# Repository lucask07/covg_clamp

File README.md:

# COVG Clamp Board 

Schematic and layout for the COVG bath and guard clamps. This board sits near electrodes and includes a force output and a high-impedance feedback input to create a closed-loop clamp. Intention is to use the same design for the bath and guard clamps of a COVG amplifiers. The board supports digital programming of the current measurement gain and the feedback loop stability. Switching on the board allows for connect and disconnect of electrodes and injection (or measurements) of calibration signals onto an electrode.

### The PDF plot of the board schematic is [here](docs/bath_clamp.pdf) 
- 2D capture of the 3D model of the clamp board layout: 
<p align="center">

## Acknowledgements 

If this work contributes to your research please cite:

I. Delgadillo Bonequi, A. Stroschein, and L. J. Koerner, “A field-programmable gate array (FPGA)-based data acquisition system for closed-loop experiments,” Review of Scientific Instruments, vol. 93, no. 11, p. 114712, Nov. 2022, [doi: 10.1063/5.0121898](http://doi.org/10.1063/5.0121898).

## HDMI: connection from DAQ to daughtercard 

The digital COVG project uses the concept of one main data acquition board connected to an FPGA. The main data acquisition board has multiple channels that extend to daughtercards. The connection to each daughtercard allows for low-latency control by connections to high-speed ADCs and DACs on the daq board. For COVG the daughtercards are the bath clamp; the guard clamp; the voltage clamp and I force; and the V1/V2. The connectivity to the daughtercard is generalized and will be the same for each. 

An HDMI-A cable is used for input and output signals that connects the bath clamp daughtercard to the DAQ board. The HDMI cable carries:

- **power**: +5V, +15V, -15V
- **GND** 
- **Analog outputs** (to ADCs): 
	- OUT\_P, OUT\_N differential pair (x1) to 5 MSPS ADC 
	- single-ended out AMP\_OUT, CAL\_ADC both to individual channel of 1 MSPS ADC (ADS8686) 
- **Analog reference**: VCM: buffered ADC common-mode voltage (nominal 2.5 V)
- **Digital inputs** (from DACs): 
	- CMD: (command signal) from 1 us settling time DAC (attenuated by x10 at board)
	- CC: (capacitive compensation) from 1 us settling time DAC. AC coupled. 
	- CAL_DAC: from 5 us settling time DAC (DAC8050). Either voltage source or current source (Howland current pump), programmable on DAQ board
- **Digital control** (I2C): SDA, SCL (@ 3.3 V levels). Pull-ups are on DAQ board not on the daughtercards! The daughtercards use a TCA9555 I/O expander to generate many control signals from the I2C interface. 
- **Utiility** grab-bag connected to test-point. Jumper on DAQ board to set to analog in, analog out or digital I/O.

| Pin | HDMI name    | Generic Daughtercard     | Bath clamp | Notes  |
|-----|--------------|--------------|------------|---------------------------------------------------------------------------|
| 1   | Data2+       | fastDAC1     | CMD        | ~1 us settling time                      |
| 2   | Data2 shield | Gnd          | Gnd        |                                                                           |
| 3   | Data2-       | Analog/GPIO1 | CAL_DAC    | Analog input signal from DAC8050, 16 bit, 5us settle, 5 V supply                                                                         |
| 4   | Data1+       | fastADC+     | IM_P       | to AD7960/AD7961. Differential low-pass filter on DAQ board                                                                          |
| 5   | Data1 shield | Gnd          | Gnd        |                                                                           |
| 6   | Data1-       | fastADC-     | IM_N       | to AD7960/AD7961. Differential low-pass filter on DAQ board                                                                          |
| 7   | Data0+       | fastDAC2     | CC         | ~1 us settling time                                                                          |
| 8   | Data0 shield | Gnd          | Gnd        |                                                                           |
| 9   | Data0-       | Analog/GPIO2 | CAL_ADC    | to ADS8686 1 MSPS, programmable PGA for range up to +/-10V                                                           |
| 10  | Clock+       | 15V          | 15V        | From a linear regulator on the DAQ board, 75 mA max per channel                                                                         |
| 11  | Clock shield | Gnd          | Gnd        |                                                                           |
| 12  | Clock-       | VCM          | VCM        | buffered on DAQ board, nominal 2.5 V                                                                          |
| 13  | CEC          | -15V         | -15V       | From a linear regulator on the DAQ board, 75 mA max per channel                             |
| 14  | Reserved     | open         | open       | Resistor jumper on DAQ board sets as analog in, analog out, or digital I/O (@ 3.3 V levels). Default stuffing option is to connect to the general purpose ADC (ADS8686). |
| 15  | SCL          | SCL          | SCL        | I2C clock. Pull-up on main DAQ board, 3.3 V levels                |
| 16  | SDA          | SDA          | SDA        | I2C data. Pull-up on main DAQ board, 3.3 V levels                 |
| 17  | Gnd          | Gnd          | Gnd        |                                                                           |
| 18  | 5V           | 5V           | 5V         | Power input from linear regulator, 200 mA max per channel (target)  |
| 19  | HPD          | Analog/GPIO3 | AMP_OUT    | output to ADS8686 1 MSPS, programmable PGA                        |

## Electrode Configurations and Modes 

### Electrodes

The electrode connections are [tip jack miniature PCB mount connectors](https://www.digikey.com/en/products/detail/cinch-connectivity-solutions-johnson/105-1103-001/241122?s=N4IgTCBcDaIIwAYCsBaOiDMKELiAugL5A) for 0.08" diameter pin connections. 

- J1 corresponds to Dagan P2 - force
- J2 corresponds to Dagan P1 - sense
- J3 corresponds to Dagan CC - capacitive compensation 

### Modes 
**Electrode diagnositcs / calibration / system ID** 

Five relays are used to:

1. Disconnect the electrodes from the active electronics (relay K2, K1). Digital control signals: *P1\_E\_CTRL*, *P2\_E\_CTRL*
2. Switch between active and passive clamp (U3). Digital control signals: *P\_CLAMP\_CTRL*
3. Connect calibration signals (ADC or DAC) to the electrodes (U4, U5). Digital control signals: *P1\_CAL\_CTRL*, *P2\_CAL\_CTRL*
A logical high digital control signal closes the Ux relays. A logical high swicthes the Kx relays so that the electronics and electrodes are disconnected. 

**Calibration** 
When "calibrating" the electrode that is driven by a DAC signal or output along the ADC signal CAL\_ADC is programmable. This output multiplexing is set by DAC\_SEL[1..4] and ADC\_SEL[1..4]. Via DAC\_SEL[1..4] an electrode can be connected to CAL\_DAC or GND. The ADC\_SEL[1..4] controls the signal that is connected to CAL\_ADC pin the options are (CAL\_SIG1, CAL\_SIG2, INAMP\_OUT, CC).   

**Clamping**

- _Voltage clamp_: U1 drives the command voltage (CMD) to electrode P2. Nominal voltage clamp mode will have all 5 relays in nominal position (with 0 coil current).  When in voltage clamp mode the current to P2 (as measured by the voltage across nets RF\_1 and P2) is output by the different ADC driver for 5 MSPS digitization. The settings for U22 (TMUX6136) are S1 = 1 for  the inamp output to be buffered out to the 5 MSPS ADC; and S2 = 1 so that the instrumentation amplifier amplifies the voltage difference: (P2 - RF_1). The voltage feedback in voltage clamp mode can be enabled/disabled by the I/O expander siganl *FDBK* (*FDBK*=0 is disabled). 

- _Current clamp_: The board has a Howland current source that can be used to set the current to P2 based upon the CMD signal (requires A2=A1=A0=0). The output current can range from +/-0.26 nA (with a 1.22 mV CMD) to +/-2.1 uA (with a 10 V CMD signal). To enable the current clamp either float or drive high the signal EN\_IPUMP. To shutoff the amplifier set EN\_IPUMP to a logical 0. When in current clamp mode the intent is that the 5 MSPS ADC measurement is of P1 (i.e. set current and measure voltage). This is accomplished by these settings for U22 (TMUX6136): S1 = 0 so that the P2 buffer output voltage is sent to the 5 MSPS ADC; and S2 = 0 so that the instrumentation amplifier amplifies P2 - 0 (RF_1 voltage will not make sense in this mode). In this mode the instrumentation amplifier output can buffer out the CAL\_OUT line to a 1 MSPS ADC channel. 

### Adjustments for clamp stability 
The P2 signal is amplified and buffered before being fedback to the main clamp amplifier (U15 within feedback\_buffer). The stability of this loop varies depending upon the load presented by the cell under test, electrode electrical characteristics, and parasitic capacitive coupling between electrodes. The stability of this feedback loop can be adjusted by modification of the feedback buffer gain and by changing the capacitance of a lead compensator at the summing junction of the main amplifier (inverting terminal). 

**Feedback buffer gain**

The feedback buffer is a non-inverting structure with an adjustable gain set by I/O expander bits RF[1..4]. The feedback resistor values are 3.01k, 12.1k, 30.1k, and 60.4k. The resistor from the inverting terminal to "ground" is 3.01k creating gains of 

- x2 = 1+3.01k/3.01k 
- x5 
- x11
- x21 

**Feedback buffer offset**

The feedback buffer has offset adjustment. This is generated by a 10-bit I2C interface DAC, IC1 (DAC53401), followed by a unipolar to bipolar amplifier (U23). The output of the bipolar converter ranges between +/-1 V (resolution of 1.9 mV / bit). OUT = VDAC*1.666-1. 

(simulation: non\_inverting\_rpot\_bw.asc)

**Compensation adjustment**

Adjustments of the closed-loop stability are achieved using four approaches. 

- The primary approach is a lead compensator formed by R30 in parallel with the capacitors in the compensation switching sheet. This method is presented in "Voltage Clamping of Excitable Membranes" by Bezanilla, Vergara, and Taylor. The compensation capacitors (47 pF, 200 pF, 1 nF, 4.7 nF) are selectable using the the TMUX6111 I/O expander bits CCOMP[1..4].
- A second approach is adjusting the gain of the feedback buffer (see above). 
- A third approach is a stabilizing feedback network of R in series with C; simulations have shown little beneift of this network. Also, beware that the C forms a pole with the current resolving resistor (R\_F) which can be very low frequency. The footprints for these components are included by not populated. This is also presented in Bezanilla, et al.
- The fourth potential approach is an input lead-lag compensator formed by R69 and C37 (unpopulated). See [TI App Note AN-1604](https://www.ti.com/lit/an/snoa486b/snoa486b.pdf?ts=1623954308102&ref_url=https%253A%252F%252Fwww.google.com%252F)

### Adjustments for current measurement

The current measurement gain (historically reported in units of mV/nA) is determined by three separate "stages".

**Resolving inline resistor**: is set by component U2 which is an analog switch (ADG1208) that determines the resistance across which the clamp current is measured. 

| Ref. Des. | Value    | mV/nA            | A2,A1,A0 | Closed Switch   | 
|-----|--------------|--------------|------------|------------|
| none -> Iclamp| n/a | n/a | 0,0,0 | Sw1 |
| R2   | 10 kOhm       |  0.01       | 0,0,1 | Sw2      | 
| R3   | 33.2 kOhm       |  0.033       | 0,1,0 | Sw3      | 
| R4   | 100k Ohm       |  0.1       | 0,1,1 | Sw4      | 
| R5   | 332 kOhm       |  0.332       | 1,0,0 | Sw4      | 
| R6   | 1 MOhm       |  1       | 1,0,1 | Sw5      | 
| R7   | 3.32 MOhm       |  3.32       | 1,1,0 | Sw6      | 
| R8   | 10 MOhm       |  10       | 1,1,1 | Sw7      | 

**Instrumentation Amplifier gain**  

There is a second stage that allows for additional gain on the analog output signal before ADC conversion. The gain of the instrumentation amplifier (AD8421) within the adc\_driver block gain is adjusted with bits G[1..3].
The gain options as controled by U17 (DG412 switch) are: 

- G = 1, G1=G2=G3=0, all switches open 
- G = 1.99, G1 = 1, others = 0 
- G = 4.98, G2 = 1, others = 0
- G = 10.00, G3 = 1, others = 0 
- G = 50, This setting is currently not programmable but set by resistors. 
- Other gains are available by combining the gain settings resistors in parallel. 

For the instrumentation amplifier Gain = 1 + 9.9 kOhm/RG 

**Output ADC driver gain**

The ADC output driver implements a gain of around 1/3 (0.308 = 499 Ohms/(1500 + 120) Ohms) to scale the maximum output of the instrumenation amplifer (+/-13.5 V) to the range of the AD796x ADC (+/-4.096 V).

**Total gain** 

(without the G = 50 option of the instrumentation amplifier) the available gain ranges are:

- min: 0.00308 mV/nA 
- max: 30.8 mV/nA. 

Since the ADC covers a range of +/-4.096 V at 16-bit resolution for step-sizes of:

- min-gain: 0.0246 LSB/nA  (40.6 nA/LSB)
- max-gain: 246.4 LSB/nA  (4.06 pA/LSB)

The amplifier noise simulates to be (very roughly) 1 nA RMS, such that ADC quantization noise will not limit amplifier performance when high-gain settings are used.

## I2C Address Table
| Component | Description | I2C address | I2C mode | 
| --------- | -------- | ------------| ------------|
| U12    | I/O expander 0: TCA9555       | 0x26 = 'b010\_0110 | Standard, Fast |
| U13    | I/O expander 1: TCA9555        | 0x20 = 'b010\_0000 | Standard, Fast |
| U6   | Unique ID EEPROM: 24AA025UID    | 0x50 = 'b101\_0000 | Standard, Fast |
| IC1   | Offset adj. DAC: DAC53401  | 0x48 = 'b100\_1000 | Standard, Fast, Fast+ |

## Current Draw

+/-15 V  (or from the +7V and -2.5 V supplies derived from +/-15 V) 

| Component | Quantity | Current [mA]| Total [mA] |
| --------- | -------- | ------------| ---------- |
| OPA828    | 2        | 5.5 | 11 |
| OPA2156   | 2 (dual) | 4.4 | 8.8 |
| OPA991S   | 1        | 0.56 | 0.56 |
| ADG1208   | 1        | 0.0001 | 0 |
| ADG1208   | 1        | 0.0001 | 0 |
| AD8421    | 1        | 2.3    | 2.3 |
| ADA4932 (ADC driver)  | 1        | 9.6    |     |
| or LMP8350 (ADC driver) |         | 15 (HP mode) | 15 |
|           |          |        | Totals (w/ LMP) |
|           |          |        |    37.66 |

## For Board and FPGA Designers

## KiCAD Setup (libraries)
Before opening the project complete these steps to setup your parts libraries. 

* On the main Kicad Menu bar click 'Preferences' -> 'Configure Paths'. 
* Then within the 'Configure Paths' window create an Environmental Variable with the 'Name' MYLIBRARY.
* Set the 'Path' to be where you will store the Digikey libraries and the COVG custom library. For example (this is on a MAC) '/Users/lucas/Documents/kicad/libraries'.

Now *git clone* (effectively download) the digikey and COVG libraries. 

* The Digikey library is at [https://github.com/Digi-Key/digikey-kicad-library](https://github.com/Digi-Key/digikey-kicad-library)
	* Use the terminal command: `git clone https://github.com/Digi-Key/digikey-kicad-library.git ` 

* The custom COVG library is at [https://github.com/lucask07/covg-kicad-lib](https://github.com/lucask07/covg-kicad-lib)
	* Use the terminal command: `git clone https://github.com/lucask07/covg-kicad-lib.git `
	* This is a private repository so will require you to request access to the repository from Lucas. 

Symbols and footprints custom to this design (and the COVG project in general) are housed in the [covg-kicad-lib repository](https://github.com/lucask07/covg-kicad-lib). This library should be a project specific library in your KiCAD *Symbol Library Management* and *Footprint Library Management*. 

* Another library in use is the [agg library](https://github.com/adamgreig/agg-kicad)

### LMP8350 ADC Driver 

Initial designs used the ADA4932-1 differential ADC driver to drive the AD7961 on the DAQ board. However, as part of the "chip shortage of 2021" there parts were hard to find in spring of 2021. An alternative part (and possibly better option) used for this board is the [LMP8350](https://rocelec.widen.net/view/pdf/d6pm6sbaz5/lmp8350.pdf?t.download=true&u=5oefqw).

## BOM (bill of materials)

The BOM is available [here](bom/bath_clamp_v1_bom.xlsx)

Two command-line tools are useful for finding and ordering the parts for the board. 

[kifield](https://xess.com/KiField/docs/_build/singlehtml/index.html): extracts all fields from components on the schematic into a spreadsheet and also allows for "injecting" updates in the spreadsheet into the schematic.

Example to extract parts:
```kifield -x covg_daq_v2.sch --recurse -i covg_daq_v2_parts.csv```

**Don't import parts from the CSV into the board! This seems to incorrectly update some components!!**:
``` kifield -x covg_daq_v2_parts.csv --recurse -i covg_daq_v2.sch ```

[kicost](https://github.com/xesscorp/KiCost) which scrapes availability and prices from various distributors and creates a spreadsheet of component cost. 

## Changelog (v1 ---> v2)
List on NB#1 pg 76.

1. Add an 'Alternate Manf#' field to all ICs (where possible). The alternative part must be pin compatible. If available add an 'Alternate2 Manf#'. If the alternative part requires a footprint change the field is 'Alternate Manf# (footprint diff)'.
2. Use +/-15 V op-amp to buffer 3.3 V into amplifier. Eliminates problem of the 3.3 V net rising since the regulator cannot sink current. 
3. Switch to a DAC with leads to improve solderability. Part chosen was the DAC101C081CIMK/NOPB.
4. Correct ADG1208 Manf# to ADG1208YRUZ so that the package matches the footprint (16-TSSOP).  
5. Switch LM337 negative regulator to MIC5270YM5-TR (alternate MIC5270-4.1YM5-TR, fixed -4.1 V).  Another option considered was the TPS7A3401DGNT. 
6. Change resistor values in adjustable regulators for lower negative voltage. The negative regulator is designed for either an adjustable version or a fixed voltage. The resistor values are 487 Ohm and 240 Ohm for -3.635 Volts. 
7. Need alternative to the AD8421 instrumentation amplifier in 8-MSOP. Locating an 8-MSOP instrumentation amplifier was challenging. Switched to an 8-SOIC footprint. 
8. The SMT SPDT relay 1462042-8 was not avaliable. The through hole version is available 1462042-7. Added new footprint to covg-library named Relay_SPDT_TE_1462042-7.
9. Need alternative to the TMUX6136 (or switch to a 4x SPST + 2 channel inverter). The findchips risk for the TMUX6136 was low so kept this part but added 0 Ohm resistors that can be populated for a default MUX configuration.
10. Mini banana  NOT YET DONE!
11. More ground test points  NOT YET DONE!
12. Fixed swap of SCL and SDA (correct by changing routing at the connector to keep other routing correct) NOT YET DONE!
13. The TCA9555DBR (IO expander) has another Manf# for the same part as TCA9555DBT. The PCA9555 is an older part that is also compatible with the TCA9555. 
14. The microchip 3.3 V regulator is not available (MCP1804T-3302I/OT). 

Use the Value field to indiciate DNI (do not install) but keep the MANF# up to date. 

## Funding 
Research reported in this publication was supported by the National Institute Of Neurological Disorders And Stroke of the National Institutes of Health under Award Number R15NS116907. The content is solely the responsibility of the authors and does not necessarily represent the official views of the National Institutes of Health.

<!---
## Block diagram - To Be Completed! 
drawio (also named add.diagrams.net) is used to create block diagrams by integrating drawio with the GitHub repository. 

--->

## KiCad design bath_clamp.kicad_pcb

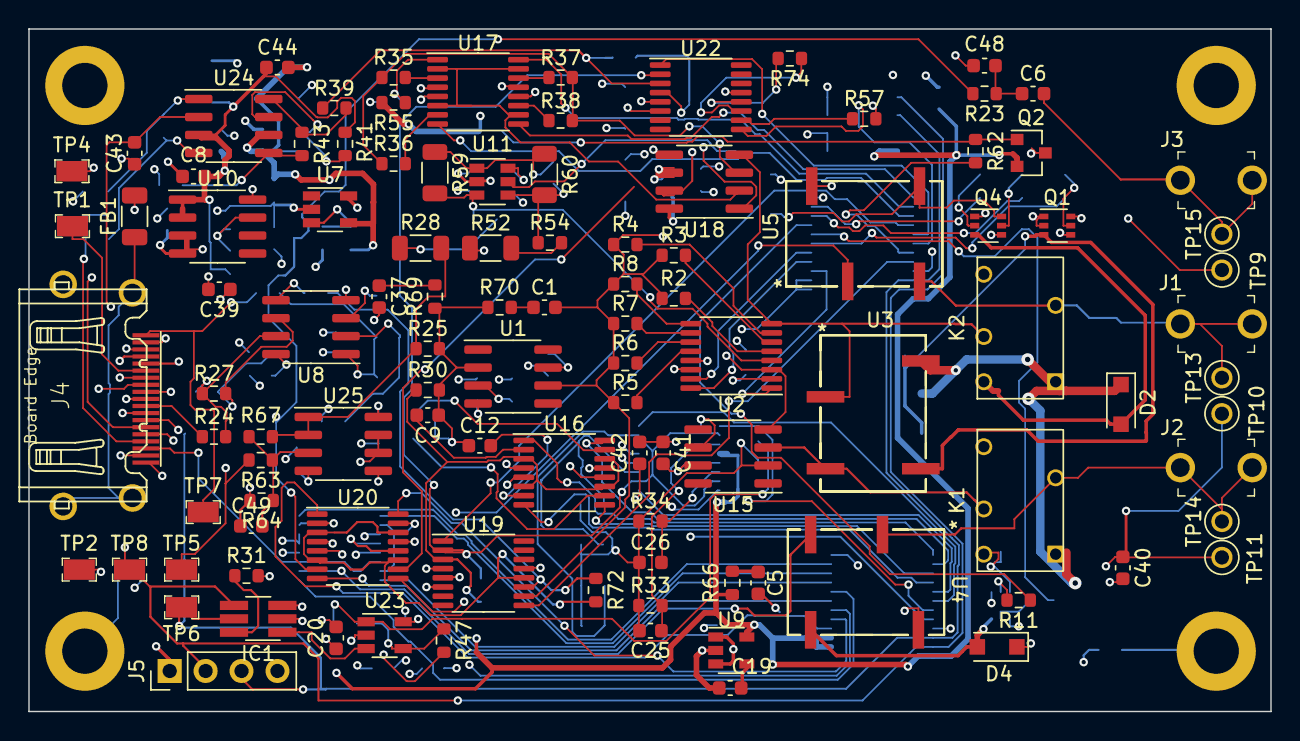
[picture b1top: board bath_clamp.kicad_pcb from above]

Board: 6 copper layers, 87.8 x 48.3 mm, 183 parts (0 on the bottom side), 138 nets.

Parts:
C1, C27, C28, C37, C48, C49: DNI; C_0603_1608Metric
C2: 1u; C_0603_1608Metric
C3: 10u; C_0805_2012Metric
C4, C7, C8, C13, C14, C20, C21, C22, C29, C30, C31, C32, C34, C35, C36, C38, C39, C40, C41, C42, C43, C44, C47: 0.1u; C_0603_1608Metric
C5: 4.7u; C_0603_1608Metric
C6: 4.7n; C_0603_1608Metric
C9: 47pF; C_0603_1608Metric
C10: 200pF; C_0603_1608Metric
C11: 1nF; C_0603_1608Metric
C12: 4.7nF; C_0603_1608Metric
C15, C16: 4.7u; C_1206_3216Metric
C17, C18, C19: 0.01u; C_0603_1608Metric
C23: 68p; C_0603_1608Metric
C24: 20p; C_0603_1608Metric
C25: 8p; C_0603_1608Metric
C26: 4p; C_0603_1608Metric
C33: 5p; C_0603_1608Metric
C45, C46: 10u; C_1206_3216Metric
D1, D2, D3, D4, D5: 1N4007; D_SOD-123F
FB1: Ferrite_Bead; C_1206_3216Metric
H1, H3, H5, H7: DNI; MountingHole_3.2mm_M3_DIN965_Pad
IC1: DAC101C081CIMK_NOPB; TSOT-23-6_HandSoldering
J1, J2, J3: 105-1103-001; Test_Jack_Horiz
J4: HDMI_A; CONN_10029449-111RLF_HDMI_A
J5: Conn_01x04; PinHeader_1x04_P2.54mm_Vertical
K1, K2: 1462042-7; Relay_SPDT_TE_1462042-7
Q1, Q3, Q4: MBT3904DW1T1G; SOT-363_SC-70-6
Q2: BC856; SOT-23
R1, R20, R23, R26, R27, R53, R54, R68, R71, R72, R73, R74: 0; R_0603_1608Metric
R2, R9, R10, R11, R12, R13, R22, R31, R38, R41, R50, R56, R62: 10k; R_0603_1608Metric
R3, R47: 33.2k; R_0603_1608Metric
R4: 100k; R_0603_1608Metric
R5: 332k; R_0603_1608Metric
R6: 1M; R_0603_1608Metric
R7: 3.32M; R_0603_1608Metric
R8: 10M; R_0603_1608Metric
R14, R17: 240; R_0603_1608Metric
R15: 487; R_0603_1608Metric
R16: 1.13k; R_0603_1608Metric
R18, R24, R44, R45, R57: 33; R_0603_1608Metric
R19, R25, R30: 20k; R_0603_1608Metric
R21: 2k; R_0603_1608Metric
R28, R52, R59, R60: 4.7M; R_1206_3216Metric
R29, R51, R55, R65, R67, R69, R70: DNI; R_0603_1608Metric
R32: 12.1k; R_0603_1608Metric
R33: 30.1k; R_0603_1608Metric
R34: 60.4k; R_0603_1608Metric
R35: 200; R_0603_1608Metric
R36: 1.1k; R_0603_1608Metric
R37: 2.49k; R_0603_1608Metric
R39, R40: 1500; R_0603_1608Metric
R42, R43: 499; R_0603_1608Metric
R46, R49: 3.01k; R_0603_1608Metric
R48: 27.4k; R_0603_1608Metric
R58: 120; R_0603_1608Metric
R61: 470k; R_0603_1608Metric
R63: 30k; R_0603_1608Metric
R64: 3k; R_0603_1608Metric
R66: 1; R_0603_1608Metric
TP1, TP2, TP4, TP5, TP6, TP7, TP8: RCT-0C; PROBE_PAD_0805
TP9, TP10, TP11: DNI; TestPoint_THTPad_D2.0mm_Drill1.0mm
TP13, TP14, TP15: TestPoint; TestPoint_THTPad_D2.0mm_Drill1.0mm
U1, U15: OPA828; SOIC-8_3.9x4.9mm_P1.27mm
U2: ADG1208; TSSOP-16_4.4x5mm_P0.65mm
U3, U4, U5: G6L-1F-TR-DC5
U6: 24AA025UID; SOIC-8_3.9x4.9mm_P1.27mm
U7: MIC5270; TSOT-23-5
U8, U25: OPA2156xD; SOIC-8_3.9x4.9mm_P1.27mm
U9: LP2981A-33DBVT; SOT-23-5
U10: LP2951_SOIC; SOIC-8_3.9x4.9mm_P1.27mm
U11: OPA991S; SOT-23-6
U12, U13: TCA9555DBR; SSOP-24_5.3x8.2mm_P0.65mm
U14, U17: DG412xUE; TSSOP-16_4.4x5mm_P0.65mm
U16, U20, U21: TMUX6111PWR; TSSOP-16_4.4x5mm_P0.65mm
U18: AD8421ARZ; SOIC-8_3.9x4.9mm_P1.27mm
U19, U22: DNI; TSSOP-16_4.4x5mm_P0.65mm
U23: OPA188xxDBV; TSOT-23-5
U24: LMP8350MA_NOPB; SOIC-8_3.9x4.9mm_P1.27mm

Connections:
3V3_BUF: R47.2, U25.6, U25.7
+3V3: C47.2, J5.4, Q2.2, R55.2, R61.1, R66.1, U6.8, U9.5, U12.2, U12.3, U12.24, U13.24, U14.12, U16.12, U20.12, U21.12, U25.5
+5V: C4.1, C20.2, C39.2, C40.2, D1.1, D2.1, D3.1, D4.1, D5.1, IC1.2, J4.18, K1.1, K2.1, R22.2, U3.8, U4.8, U5.8, U9.1, U9.3, U17.12
+7V: C8.1, C17.2, C44.2, C45.2, R16.2, R41.2, U10.1, U10.2, U24.3
+15V: C7.1, C14.2, C16.2, C21.2, C30.2, C32.2, C35.2, C38.2, C41.2, J4.10, U1.7, U2.13, U8.8, U10.8, U11.6, U14.13, U15.7, U16.13, U17.13, U18.8, U19.13, U20.13, U21.13, U22.13, U23.5, U25.8
-2V5: C3.2, C18.2, C44.1, C46.2, R15.2, R65.1, U7.4, U24.6
-15V: C2.2, C13.2, C15.2, C22.1, C29.2, C31.2, C34.2, C36.2, C42.1, J4.13, U1.4, U2.3, U7.5, U8.4, U11.2, U14.4, U15.4, U16.4, U17.4, U18.5, U19.5, U20.4, U21.4, U22.5, U23.2, U25.4
/SCL: IC1.5, J4.15, J5.3, TP6.1, U6.6, U12.22, U13.22
/SDA: IC1.4, J4.16, J5.2, TP8.1, U6.5, U12.23, U13.23
/bath_clamp_top/A0: U2.1, U13.4
/bath_clamp_top/A1: U2.16, U13.5
/bath_clamp_top/A2: U2.15, U13.6
/bath_clamp_top/ADC_SEL1: U12.4, U20.1
/bath_clamp_top/ADC_SEL2: U12.5, U20.16
/bath_clamp_top/ADC_SEL3: U12.6, U20.9
/bath_clamp_top/ADC_SEL4: U12.7, U20.8
/bath_clamp_top/AMP_OUT: J4.19, R18.1, TP7.1
/bath_clamp_top/CAL_ADC: J4.9, R24.1
/bath_clamp_top/CAL_DAC: J4.3, U21.3, U21.14
/bath_clamp_top/CAL_OUT: R72.2, U19.12, U20.3, U20.6, U20.11, U20.14
/bath_clamp_top/CAL_SIG1: U4.4, U20.2, U21.2, U21.7
/bath_clamp_top/CAL_SIG2: U5.2, U20.15, U21.10, U21.15
/bath_clamp_top/CC: J4.7, R23.2, U20.7
/bath_clamp_top/CCOMP1: U12.13, U16.1
/bath_clamp_top/CCOMP2: U12.14, U16.16
/bath_clamp_top/CCOMP3: U12.15, U16.9
/bath_clamp_top/CCOMP4: U12.16, U16.8
/bath_clamp_top/CMD: J4.1, R63.2, TP5.1
/bath_clamp_top/CMD_BUF: R25.1, R28.2, R67.1, U25.1, U25.2
/bath_clamp_top/DAC_SEL1: U12.8, U21.1
/bath_clamp_top/DAC_SEL2: U12.9, U21.16
/bath_clamp_top/DAC_SEL3: U12.10, U21.9
/bath_clamp_top/DAC_SEL4: U12.11, U21.8
/bath_clamp_top/EN: R22.1, U2.2
/bath_clamp_top/EN_IPUMP: R62.2, U13.19
/bath_clamp_top/FDBK: U13.16, U19.1
/bath_clamp_top/F_MUX_OUT: R30.1, R68.1, U16.3, U16.6, U16.11, U16.14, U19.3
/bath_clamp_top/G1: U13.13, U17.9
/bath_clamp_top/G2: U13.14, U17.16
/bath_clamp_top/G3: U13.15, U17.8
/bath_clamp_top/INAMP_OUT: R73.2, U18.7, U20.10, U22.4
/bath_clamp_top/OUT_N: J4.6, R45.2
/bath_clamp_top/OUT_P: J4.4, R44.2
/bath_clamp_top/P1: K1.7, U3.4, U15.3
/bath_clamp_top/P1_BUF: R1.2, R68.2, U14.2, U14.6, U14.10, U14.15, U15.6, U19.2, U22.2
/bath_clamp_top/P1_CAL: D4.2, Q3.6, U4.5
/bath_clamp_top/P1_CAL_CTRL: R11.1, U13.9
/bath_clamp_top/P1_E: D1.2, K1.8, Q3.3
/bath_clamp_top/P1_E_CTRL: R12.1, U13.8
/bath_clamp_top/P1_OUT: J2.1, K1.3, TP14.1, U4.2
/bath_clamp_top/P2: K2.7, U2.8, U3.2, U18.4
/bath_clamp_top/P2_CAL_CTRL: R9.2, U13.11
/bath_clamp_top/P2_E_CTRL: R10.2, U13.10
/bath_clamp_top/P2_OUT: J1.1, K2.3, TP13.1, U5.4
/bath_clamp_top/PCLAMP_CTRL: R13.2, U13.7
/bath_clamp_top/RF1: U12.17, U14.1
/bath_clamp_top/RF2: U12.18, U14.8
/bath_clamp_top/RF3: U12.19, U14.9
/bath_clamp_top/RF4: U12.20, U14.16
/bath_clamp_top/RF_1: C1.2, R2.1, R3.1, R4.1, R5.1, R6.1, R7.1, R8.1, R74.2, U1.6, U19.10, U22.12
/bath_clamp_top/RF_1_OUT: U13.20, U19.9
/bath_clamp_top/S1: U13.17, U22.1
/bath_clamp_top/S2: U13.18, U22.9
/bath_clamp_top/VCM: C43.2, J4.12, U24.2
/bath_clamp_top/V_GND: C9.1, C10.1, C11.1, C12.1, R25.2, R30.2, R69.1, R70.1, U1.2
/bath_clamp_top/adc_driver/G4: R55.1, R56.2, U17.1
/bath_clamp_top/adc_driver/LMP_EN: R41.1, R65.2, U24.7
/bath_clamp_top/howland_ipump/I_OUT: R53.1, R59.2, U2.4, U11.3
GND: C2.1, C3.1, C4.2, C5.2, C7.2, C8.2, C13.1, C14.1, C15.1, C16.1, C17.1, C18.1, C19.2, C20.1, C21.1, C22.2, C29.1, C30.1, C31.1, C32.1, C34.1, C35.1, C36.1, C37.2, C38.1, C39.1, C40.1, C41.1, C42.2, C43.1, C45.1, C46.1, C47.1, C48.2, C49.1, FB1.2, IC1.3, J4.2, J4.5, J4.8, J4.11, J4.17, J5.1, Q1.1, Q1.2, Q1.4, Q1.6, Q3.1, Q3.4, Q4.1, Q4.4, R14.1, R17.1, R21.2, R26.2, R29.2, R31.2, R48.1, R51.2, R52.2, R56.1, R57.2, R58.1, R64.2, R71.2, TP2.1, TP4.1, TP9.1, TP10.1, TP11.1, U2.14, U6.1, U6.2, U6.3, U6.4, U7.2, U9.2, U10.3, U10.4, U12.12, U12.21, U13.2, U13.3, U13.12, U13.21, U14.5, U16.5, U17.5, U18.6, U19.4, U19.6, U20.5, U21.5, U21.6, U21.11, U22.6
unnamed: C1.1, R70.2
unnamed: C5.1, R66.2
unnamed: C6.2, J3.1, TP15.1
unnamed: C9.2, U16.2
unnamed: C10.2, U16.15
unnamed: C11.2, U16.10
unnamed: C12.2, U16.7
unnamed: C19.1, U9.4
unnamed: C23.1, C24.1, C25.1, C26.1, R32.1, R33.1, R34.1, R46.1, R49.1, U15.2
unnamed: C23.2, R46.2, U14.3
unnamed: C24.2, R32.2, U14.7
unnamed: C25.2, R33.2, U14.11
unnamed: C26.2, R34.2, U14.14
unnamed: C27.1, R19.2, R21.1, U8.2
unnamed: C27.2, R18.2, R19.1, U8.1
unnamed: C28.1, R27.2, R29.1, U8.6
unnamed: C28.2, R24.2, R27.1, U8.7
unnamed: C33.1, R54.1, R60.2, U11.4
unnamed: C33.2, R59.1, R60.1, U11.1
unnamed: C37.1, R69.2
unnamed: C6.1, C48.1, R23.1
unnamed: C49.2, R63.1, R64.1, R67.2, U25.3
unnamed: D2.2, K2.8, Q4.3
unnamed: D3.2, Q1.3, U3.5
unnamed: D5.2, Q4.6, U5.5
unnamed: FB1.1, J4.SH
unnamed: H1.1, R51.1
unnamed: H5.1, R71.1
unnamed: IC1.1, U23.3
unnamed: IC1.6, R31.1
unnamed: J4.14, TP1.1
unnamed: Q1.5, R13.1
unnamed: Q2.1, R61.2, R62.1
unnamed: Q2.3, U11.5
unnamed: Q3.2, R11.2
unnamed: Q3.5, R12.2
unnamed: Q4.2, R9.1
unnamed: Q4.5, R10.1
unnamed: R1.1, U8.3
unnamed: R2.2, U2.5
unnamed: R3.2, U2.6
unnamed: R4.2, U2.7
unnamed: R5.2, U2.12
unnamed: R6.2, U2.11
unnamed: R7.2, U2.10
unnamed: R8.2, U2.9
unnamed: R14.2, R15.1, U7.3
unnamed: R16.1, R17.2, U10.7
unnamed: R20.1, U8.5
unnamed: R20.2, R72.1, U19.11
unnamed: R26.1, U1.3
unnamed: R28.1, R53.2
unnamed: R35.1, R36.1, R37.1, R38.1, U18.3
unnamed: R35.2, U17.3
unnamed: R36.2, U17.7
unnamed: R37.2, U17.14
unnamed: R38.2, U17.11
unnamed: R39.1, R43.1, U24.8
unnamed: R39.2, R73.1, U22.3
unnamed: R40.1, R58.2
unnamed: R40.2, R42.2, U24.1
unnamed: R42.1, R44.1, U24.4
unnamed: R43.2, R45.1, U24.5
unnamed: R47.1, R48.2, R50.2, U23.4
unnamed: R49.2, R50.1, U23.1
unnamed: R52.1, R54.2
unnamed: R57.1, U22.10
unnamed: R74.1, U18.1, U22.11
unnamed: U17.2, U17.6, U17.10, U17.15, U18.2

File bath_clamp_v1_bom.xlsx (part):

Refs | Alternative MPN | Arrow Part Number | Arrow Price/Stock | Category | DK_Datasheet_Link | DK_Detail_Page | Description | Digi-Key_PN | Family | Height | MPN | Manf# | Manufacturer | Manufacturer_Name | Manufacturer_Part_Number | Mouser Part Number | Mouser Price/Stock | PARTREV | STANDARD | Status | Tolerance | datasheet | footprint | value | voltage
C1 |  |  |  |  |  |  |  |  |  |  |  |  |  |  |  |  |  |  |  |  |  | ~ | Capacitor_SMD:C_0603_1608Metric | DNI
C10 |  |  |  |  |  |  |  |  |  |  |  | CC0603JRNPO9BN221 |  |  |  |  |  |  |  |  |  | ~ | Capacitor_SMD:C_0603_1608Metric | 200pF | 50V
C11 |  |  |  |  |  |  |  |  |  |  |  | CC0603JRNPO9BN102 |  |  |  |  |  |  |  |  | 5% | ~ | Capacitor_SMD:C_0603_1608Metric | 1nF | 50V
C12 | CL10C332JB8NNNC |  |  |  |  |  |  |  |  |  |  | CC0603JRNPO9BN332 |  |  |  |  |  |  |  |  | 5% | ~ | Capacitor_SMD:C_0603_1608Metric | 4.7nF | 50V
C13 |  |  |  |  |  |  |  |  |  |  |  | CC0603MRX7R8BB104 |  |  |  |  |  |  |  |  | 20% | ~ | Capacitor_SMD:C_0603_1608Metric | 0.1u | 25V
C14 |  |  |  |  |  |  |  |  |  |  |  | CC0603MRX7R8BB104 |  |  |  |  |  |  |  |  |  | ~ | Capacitor_SMD:C_0603_1608Metric | 0.1u | 25V
C15 |  |  |  |  |  |  |  |  |  |  |  | CL31B475KAHNFNE |  |  |  |  |  |  |  |  | 10% | ~ | Capacitor_SMD:C_1206_3216Metric | 4.7u | 25V
C16 |  |  |  |  |  |  |  |  |  |  |  | CL31B475KAHNFNE |  |  |  |  |  |  |  |  | 10% | ~ | Capacitor_SMD:C_1206_3216Metric | 4.7u | 25V
C17 |  |  |  |  |  |  |  |  |  |  |  | CC0603MRX7R8BB104 |  |  |  |  |  |  |  |  | 20% | ~ | Capacitor_SMD:C_0603_1608Metric | 0.1u | 25V
C18 |  |  |  |  |  |  |  |  |  |  |  | CC0603MRX7R8BB104 |  |  |  |  |  |  |  |  | 20% | ~ | Capacitor_SMD:C_0603_1608Metric | 0.1u | 25V
C19 |  |  |  |  |  |  |  |  |  |  |  | CL10B225KP8NNNC |  |  |  |  |  |  |  |  | 10% | ~ | Capacitor_SMD:C_0603_1608Metric | 2.2u | 10V
C2 |  |  |  |  |  |  |  |  |  |  |  | CC0603MRX7R8BB104 |  |  |  |  |  |  |  |  | 20% | ~ | Capacitor_SMD:C_0603_1608Metric | 0.1u | 25V
C20 |  |  |  |  |  |  |  |  |  |  |  | CC0603MRX7R8BB104 |  |  |  |  |  |  |  |  | 20% | ~ | Capacitor_SMD:C_0603_1608Metric | 0.1u | 25V
C21 |  |  |  |  |  |  |  |  |  |  |  | CC0603MRX7R8BB104 |  |  |  |  |  |  |  |  | 20% | ~ | Capacitor_SMD:C_0603_1608Metric | 0.1u | 25V
C22 |  |  |  |  |  |  |  |  |  |  |  | CC0603MRX7R8BB104 |  |  |  |  |  |  |  |  | 20% | ~ | Capacitor_SMD:C_0603_1608Metric | 0.1u | 25V
C23 |  |  |  |  |  |  |  |  |  |  |  |  |  |  |  |  |  |  |  |  | 20% | ~ | Capacitor_SMD:C_0603_1608Metric | 70p | 25V
C24 |  |  |  |  |  |  |  |  |  |  |  |  |  |  |  |  |  |  |  |  | 20% | ~ | Capacitor_SMD:C_0603_1608Metric | 20p | 25V
C25 |  |  |  |  |  |  |  |  |  |  |  |  |  |  |  |  |  |  |  |  | 20% | ~ | Capacitor_SMD:C_0603_1608Metric | 8p | 25V
C26 |  |  |  |  |  |  |  |  |  |  |  |  |  |  |  |  |  |  |  |  | 20% | ~ | Capacitor_SMD:C_0603_1608Metric | 4p | 25V
C27 |  |  |  |  |  |  |  |  |  |  |  |  |  |  |  |  |  |  |  |  |  | ~ | Capacitor_SMD:C_0603_1608Metric | DNI
C28 |  |  |  |  |  |  |  |  |  |  |  |  |  |  |  |  |  |  |  |  |  | ~ | Capacitor_SMD:C_0603_1608Metric | DNI
C29 |  |  |  |  |  |  |  |  |  |  |  | CC0603MRX7R8BB104 |  |  |  |  |  |  |  |  | 20% | ~ | Capacitor_SMD:C_0603_1608Metric | 0.1u | 25V
C3 |  |  |  |  |  |  |  |  |  |  |  | CC0603JRX7R9BB472 |  |  |  |  |  |  |  |  | 5% | ~ | Capacitor_SMD:C_0603_1608Metric | 5p | 50V
C30 |  |  |  |  |  |  |  |  |  |  |  | CC0603MRX7R8BB104 |  |  |  |  |  |  |  |  |  | ~ | Capacitor_SMD:C_0603_1608Metric | 0.1u | 25V
C31 |  |  |  |  |  |  |  |  |  |  |  | CC0603MRX7R8BB104 |  |  |  |  |  |  |  |  | 20% | ~ | Capacitor_SMD:C_0603_1608Metric | 0.1u | 25V
C32 |  |  |  |  |  |  |  |  |  |  |  | CC0603MRX7R8BB104 |  |  |  |  |  |  |  |  |  | ~ | Capacitor_SMD:C_0603_1608Metric | 0.1u | 25V
C33 |  |  |  |  |  |  |  |  |  |  |  | CC0603JRX7R9BB472 |  |  |  |  |  |  |  |  | 5% | ~ | Capacitor_SMD:C_0603_1608Metric | 5p | 50V
C34 |  |  |  |  |  |  |  |  |  |  |  | CC0603MRX7R8BB104 |  |  |  |  |  |  |  |  | 20% | ~ | Capacitor_SMD:C_0603_1608Metric | 0.1u | 25V
C35 |  |  |  |  |  |  |  |  |  |  |  | CC0603MRX7R8BB104 |  |  |  |  |  |  |  |  |  | ~ | Capacitor_SMD:C_0603_1608Metric | 0.1u | 25V
C36 |  |  |  |  |  |  |  |  |  |  |  | CC0603MRX7R8BB104 |  |  |  |  |  |  |  |  | 20% | ~ | Capacitor_SMD:C_0603_1608Metric | 0.1u | 25V
C37 |  |  |  |  |  |  |  |  |  |  |  | CC0603MRX7R8BB104 |  |  |  |  |  |  |  |  | 20% | ~ | Capacitor_SMD:C_0603_1608Metric | DNI | 25V
C38 |  |  |  |  |  |  |  |  |  |  |  | CC0603MRX7R8BB104 |  |  |  |  |  |  |  |  |  | ~ | Capacitor_SMD:C_0603_1608Metric | 0.1u | 25V
C4 |  |  |  |  |  |  |  |  |  |  |  | CC0603MRX7R8BB104 |  |  |  |  |  |  |  |  | 20% | ~ | Capacitor_SMD:C_0603_1608Metric | 0.1u | 25V
C5 |  |  |  |  |  |  |  |  |  |  |  | CC0603MRX7R8BB104 |  |  |  |  |  |  |  |  |  | ~ | Capacitor_SMD:C_0603_1608Metric | 0.1u | 25V
C6 |  |  |  |  |  |  |  |  |  |  |  | CC0603JRX7R9BB472 |  |  |  |  |  |  |  |  | 5% | ~ | Capacitor_SMD:C_0603_1608Metric | 4.7n | 50V
C7 |  |  |  |  |  |  |  |  |  |  |  | CC0603MRX7R8BB104 |  |  |  |  |  |  |  |  | 20% | ~ | Capacitor_SMD:C_0603_1608Metric | 0.1u | 25V
C8 |  |  |  |  |  |  |  |  |  |  |  | CC0603MRX7R8BB104 |  |  |  |  |  |  |  |  | 20% | ~ | Capacitor_SMD:C_0603_1608Metric | 0.1u | 25V
C9 |  |  |  |  |  |  |  |  |  |  |  | CC0603JRNPO9BN470 |  |  |  |  |  |  |  |  | 5% | ~ | Capacitor_SMD:C_0603_1608Metric | 47pF | 50V
D1 |  |  |  |  |  |  |  |  |  |  |  | 1N4007FLTR |  |  |  |  |  |  |  |  |  | http://www.smc-diodes.com/propdf/1N4001FL-1N4007FL%20N1646%2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 | Diode_SMD:D_SOD-123F | 1N4007
D2 |  |  |  |  |  |  |  |  |  |  |  | 1N4007FLTR |  |  |  |  |  |  |  |  |  | http://www.smc-diodes.com/propdf/1N4001FL-1N4007FL%20N1646%2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 | Diode_SMD:D_SOD-123F | 1N4007
D3 |  |  |  |  |  |  |  |  |  |  |  | 1N4007FLTR |  |  |  |  |  |  |  |  |  | http://www.smc-diodes.com/propdf/1N4001FL-1N4007FL%20N1646%2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 | Diode_SMD:D_SOD-123F | 1N4007
D4 |  |  |  |  |  |  |  |  |  |  |  | 1N4007FLTR |  |  |  |  |  |  |  |  |  | http://www.smc-diodes.com/propdf/1N4001FL-1N4007FL%20N1646%2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 | Diode_SMD:D_SOD-123F | 1N4007
D5 |  |  |  |  |  |  |  |  |  |  |  | 1N4007FLTR |  |  |  |  |  |  |  |  |  | http://www.smc-diodes.com/propdf/1N4001FL-1N4007FL%20N1646%2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 | Diode_SMD:D_SOD-123F | 1N4007
H1 |  |  |  |  |  |  |  |  |  |  |  |  |  |  |  |  |  |  |  |  |  | ~ | MountingHole:MountingHole_3.2mm_M3_DIN965_Pad | MountingHole_Pad
H3 |  |  |  |  |  |  |  |  |  |  |  |  |  |  |  |  |  |  |  |  |  | ~ | MountingHole:MountingHole_3.2mm_M3_DIN965_Pad | MountingHole_Pad
H5 |  |  |  |  |  |  |  |  |  |  |  |  |  |  |  |  |  |  |  |  |  | ~ | MountingHole:MountingHole_3.2mm_M3_DIN965_Pad | MountingHole_Pad
H7 |  |  |  |  |  |  |  |  |  |  |  |  |  |  |  |  |  |  |  |  |  | ~ | MountingHole:MountingHole_3.2mm_M3_DIN965_Pad | MountingHole_Pad
IC1 |  | DAC53401DSGR | https://www.arrow.com/en/products/dac53401dsgr/texas-instruments |  |  |  | Digital to Analog Converters - DAC 10-bit 1-channel DAC with NVM, buffered volt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 |  |  | 0.8 |  |  |  | Texas Instruments | DAC53401DSGR | 595-DAC53401DSGR | https://www.mouser.co.uk/ProductDetail/Texas-Instruments/DAC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 |  |  |  |  | http://www.ti.com/lit/ds/symlink/dac53401.pdf?HQS=TI-null-nu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 | covg-kicad:WSON-8-1EP_2x2mm_P0.5mm_EP0.9x1.6mm_posMask | DAC53401DSGR
J1 |  |  |  | Connectors, Interconnects | https://belfuse.com/resources/Johnson/drawings/dr-1051101001.pdf | /product-detail/en/cinch-connectivity-solutions-johnson/105-1103-001/J577-ND/24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 | CONN TIP JACK SOLDER BLACK | J577-ND | Banana and Tip Connectors - Jacks, Plugs |  | 105-1103-001 | 105-1103-001 |  |  |  |  |  |  |  | Active |  | https://belfuse.com/resources/Johnson/drawings/dr-1051101001.pdf | digikey-footprints:Test_Jack_Horiz | 105-1103-001
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
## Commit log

2021-05-07 update gitignore
2021-05-07 updates to README
2021-05-12 offset adjust to feedback buffer
2021-05-13 reduced ERC to just 4 warnings
2021-05-13 updates to pcb layout
2021-05-13 Added test_github.drawio
2021-05-13 Added test_github.svg
2021-05-14 added switching (partially) for current clamp
2021-05-17 before adding Howland for current clamp
2021-05-23 update MUX for adc driver
2021-05-26 added pdf print of schematics
2021-05-28 made sheet for Howland
2021-06-08 removed all references to clamp footprints
2021-06-08 removed clamp footprints
2021-06-11 layout updates; part positioning
2021-06-13 first freerouter trial of routing
2021-06-14 layout updates and 3d models
2021-06-17 README updates
2021-06-18 freerouter updates; close to submission
2021-06-22 updates to schematic plot
2021-07-02 before autoroute
2021-07-08 clamp files at submission to JLCPCB
2022-01-19 updating git so that kicad schematic matches pdf doc
2022-03-23 renamed files to remove version number
2022-03-23 added many alternate manufacturing part numbers
2022-04-02 updates to schematic for alternate part #s
2022-04-05 nearly completed layout re-route
2022-04-12 gerbers, BOM and fabrication files sent to PCBway
2022-06-01 add PDF print of schematic
2022-06-01 remove .zip backups from remote

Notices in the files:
parts and their libraries:
Copyright 2016 Accelerated Designs. All rights reserved.
